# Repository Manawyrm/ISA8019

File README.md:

# ISA8019
ISA8019 is a modern, open-source hardware design for an ISA-bus network card.
It uses an RTL8019 chipset and is NE2000-compatible, which makes it easy to use with just about any operating system or software available. 

The design is optimized for automated assembly at [JLCPCB](https://jlcpcb.com/DDE). 

Only the RJ45 jack, jumper headers and the DIP-32 socket for the Boot ROM have to be soldered. 
Jumpers and Boot ROM are optional, the card can be used without any jumpers configured. 

Configuration can be done in 3 modes: 
- Jumper mode (JP jumper set)  
This mode allows for manual configuration of any parameters (I/O address, IRQ, BROM address & size, etc.) manually via jumpers. Refer to the back of the PCB for details. 
- EEPROM mode (also called "Jumperless", no jumpers set)  
In this mode, all parameters can be configured via the RSET8019.EXE dos utility and will be stored in the 9364 I²C EEPROM.
- PNP mode (no jumpers set)  
For modern computers and operating systems like Windows 9x or Linux, this mode is ideal. Resource management will be done by the BIOS or OS.

### Details
[Rev. A - Schematic](PCB/gerbers/RevA/ISA8019.pdf)  
[Rev. A - Interactive BOM](https://tbspace.de/content/downloads/isa8019_ibom.html)  
[Rev. A - Gerbers & Production files](PCB/gerbers/RevA/ISA8019/ISA8019.zip)  

### Drivers
[Official Realtek drivers, Windows 3.11, 9x, NT](https://github.com/Manawyrm/ISA8019/tree/master/Drivers/Official%20Realtek%20drivers)  
[MS-DOS packet drivers, for 16-bit machines](Drivers/Crynwr%20packet%20driver%20-%2016bit%20ISA)  
[MS-DOS packet drivers, modded for 8-bit XT machines](Drivers/Crynwr%20packet%20driver%20-%20modified%20for%208bit%20operation)  

### Programming utilities
[RSET8019.EXE](Programming%20utilities/Rset8019.exe) for DOS, can set EEPROM parameters, also includes diagnostic functions  
[pg8019](Programming%20utilities/pg8019) for DOS, can initialize EEPROM, set MAC address, vendor/product IDs  

### Errata
Rev.A - Soldermask over ISA slot

[https://tbspace.de](https://tbspace.de)

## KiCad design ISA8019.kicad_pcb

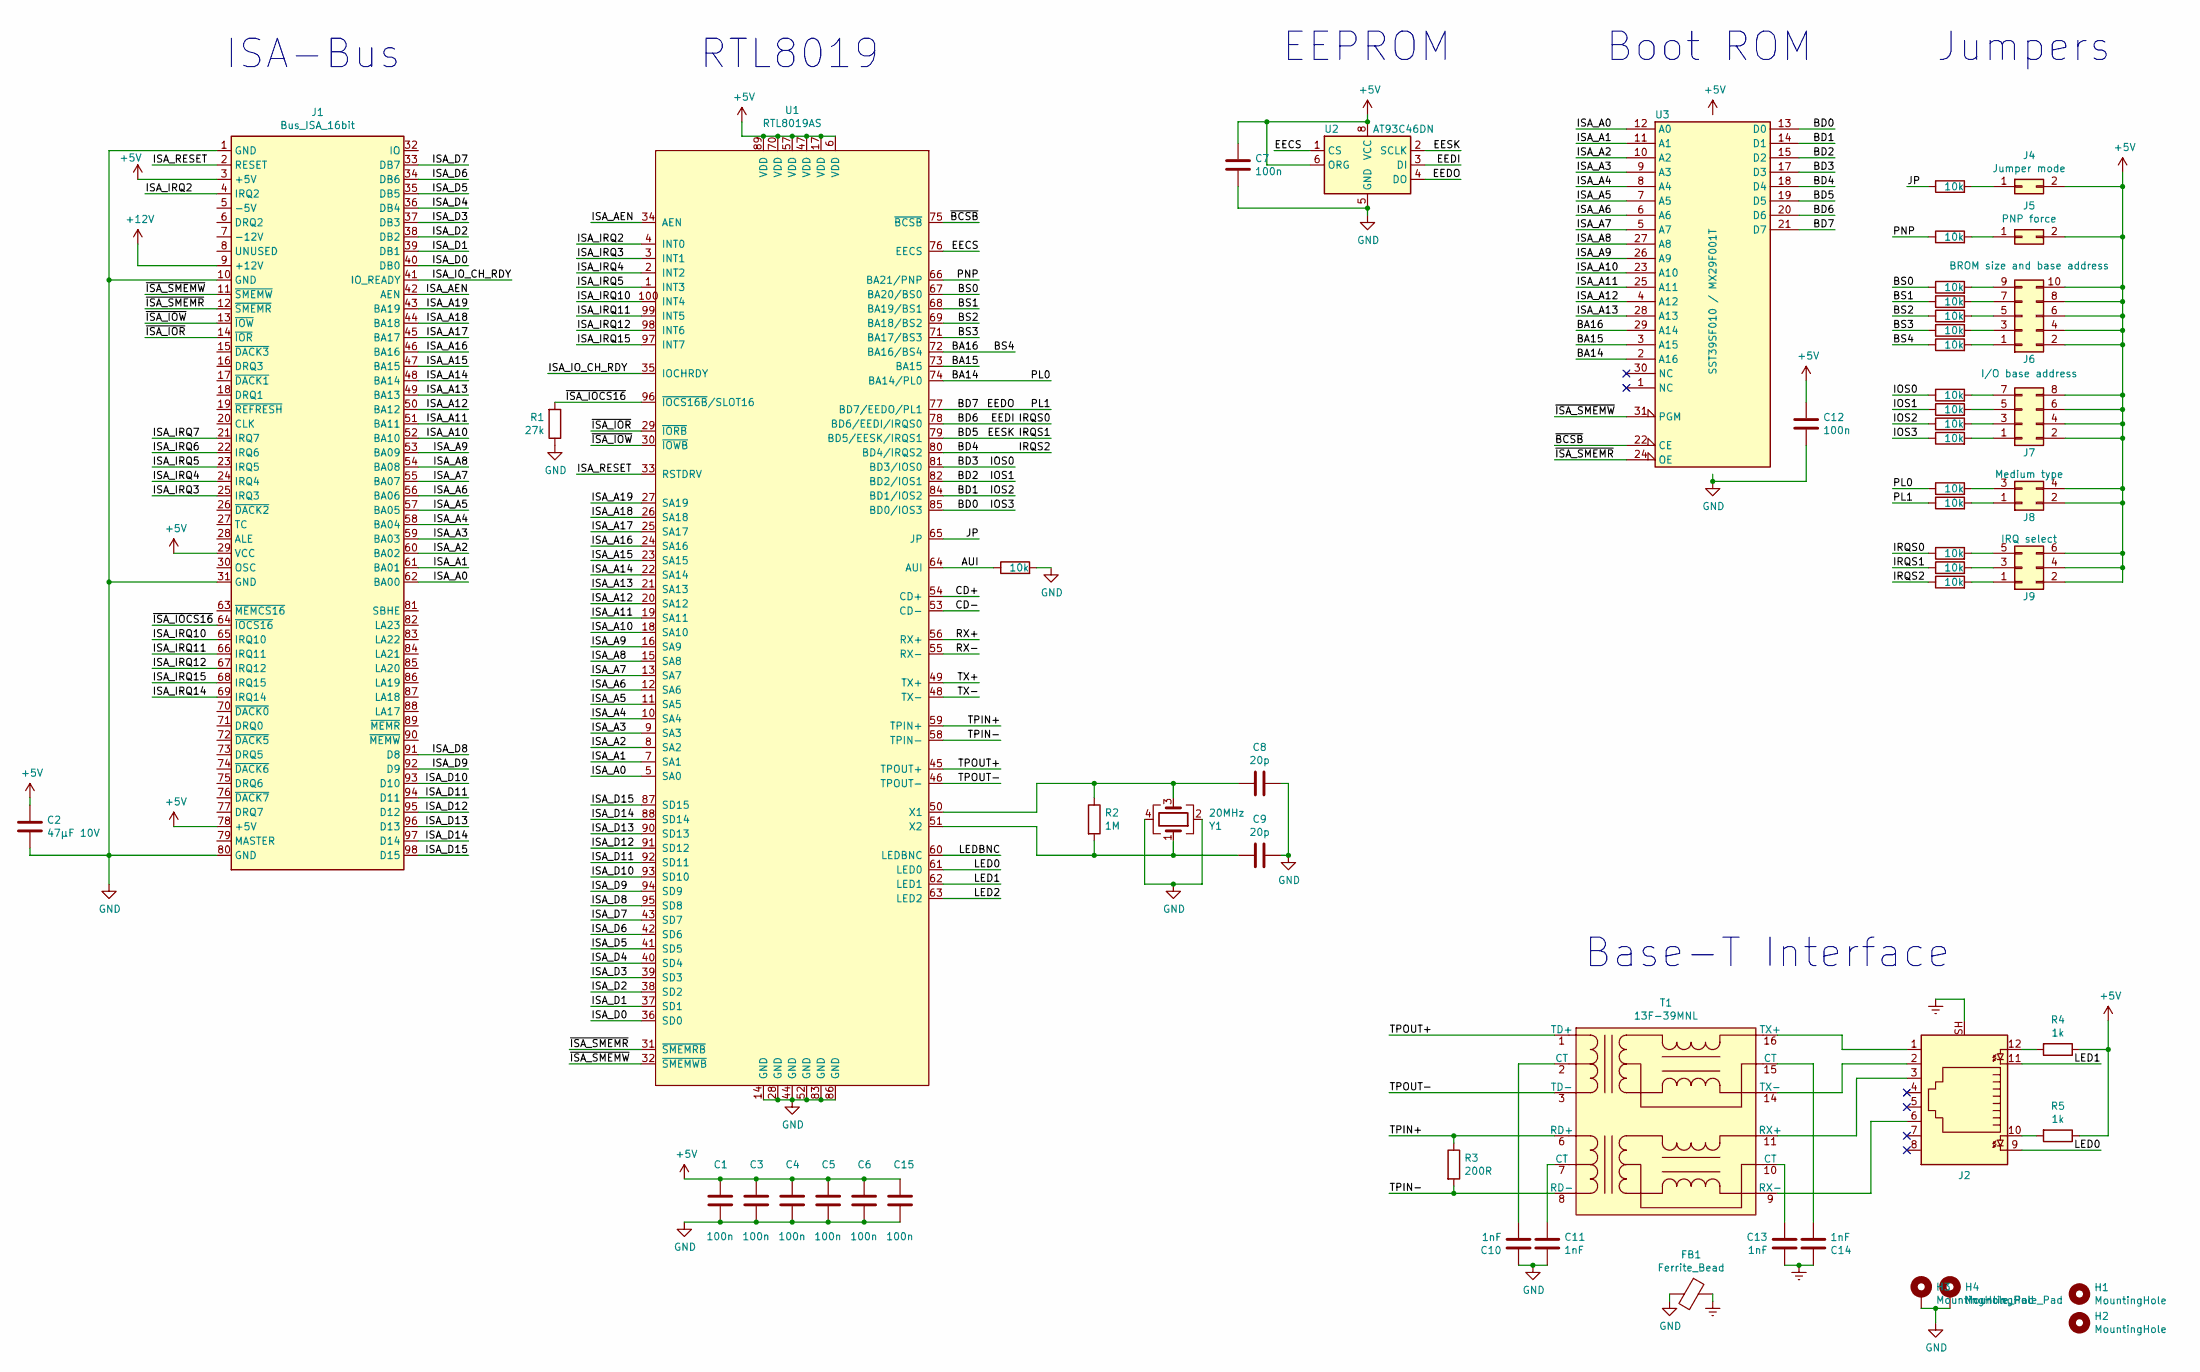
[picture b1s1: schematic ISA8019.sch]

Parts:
C1, C3, C4, C5, C6, C7, C12, C15: 100n; C_0402_1005Metric; LCSC C1525
C2: 47µF 10V; C_1206_3216Metric; LCSC C96123
C8, C9: 20p; C_0402_1005Metric; LCSC C1554
C10, C11, C13, C14: 1nF; C_1206_3216Metric; LCSC C9196
FB1: Ferrite_Bead; L_0805_2012Metric; LCSC C1017
H1, H2: MountingHole; ToolingHole_JLCSMT
H3, H4: MountingHole_Pad; MountingHole_3.2mm_M3_Pad_Via
J1: Bus_ISA_16bit; BUS_AT
J2: 8P8C_Shielded; 8P8C_yellow_green_Ckmtw_C133529
J4: Jumper mode; PinHeader_2x01_P2.54mm_Vertical
J5: PNP force; PinHeader_2x01_P2.54mm_Vertical
J6: BROM size and base address; PinHeader_2x05_P2.54mm_Vertical
J7: I/O base address; PinHeader_2x04_P2.54mm_Vertical
J8: Medium type; PinHeader_2x02_P2.54mm_Vertical
J9: IRQ select; PinHeader_2x03_P2.54mm_Vertical
R1: 27k; R_0402_1005Metric; LCSC C25771
R2: 1M; R_0402_1005Metric; LCSC C26083
R3: 200R; R_0402_1005Metric; LCSC C25087
R4, R5: 1k; R_0402_1005Metric; LCSC C11702
R6, R7, R8, R9, R10, R11, R12, R13, R14, R15, R16, R17, R18, R19, R20, R21, R22: 10k; R_0402_1005Metric; LCSC C25744
T1: 13F-39MNL; SOIC-16W-12_7.5x10.3mm_P1.27mm; LCSC C115949
U1: RTL8019AS; LQFP-14x20mm_P0.5mm; LCSC C10016
U2: AT93C46DN; SOIC-8_3.9x4.9mm_P1.27mm; LCSC C6499
U3: SST39SF010 / MX29F001T; DIP-32_W15.24mm_Socket_LongPads
Y1: 20MHz; Crystal_SMD_3225-4Pin_3.2x2.5mm; LCSC C110936

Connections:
+5V: C1.1, C2.1, C3.1, C4.1, C5.1, C6.1, C7.1, C12.1, C15.1, J1.3 (+5V), J1.29 (VCC), J1.78 (+5V), J4.2, J5.2, J6.2, J6.4, J6.6, J6.8, J6.10, J7.2, J7.4, J7.6, J7.8, J8.2, J8.4, J9.2, J9.4, J9.6, R4.1, R5.1, U1.6 (VDD), U1.17 (VDD), U1.47 (VDD), U1.57 (VDD), U1.70 (VDD), U1.89 (VDD), U2.6 (ORG), U2.8 (VCC), U3.32 (VCC)
+12V: J1.9 (+12V)
/AUI: R6.1, U1.64 (AUI)
/BA14: R18.1, U1.74 (BA14/PL0), U3.2 (A16)
/BA15: U1.73 (BA15), U3.3 (A15)
/BA16: R13.1, U1.72 (BA16/BS4), U3.29 (A14)
/BD0: R17.1, U1.85 (BD0/IOS3), U3.13 (D0)
/BD1: R16.1, U1.84 (BD1/IOS2), U3.14 (D1)
/BD2: R15.1, U1.82 (BD2/IOS1), U3.15 (D2)
/BD3: R14.1, U1.81 (BD3/IOS0), U3.17 (D3)
/BD4: R22.1, U1.80 (BD4/IRQS2), U3.18 (D4)
/BD5: R21.1, U1.79 (BD5/EESK/IRQS1), U2.2 (SCLK), U3.19 (D5)
/BD6: R20.1, U1.78 (BD6/EEDI/IRQS0), U2.3 (DI), U3.20 (D6)
/BD7: R19.1, U1.77 (BD7/EEDO/PL1), U2.4 (DO), U3.21 (D7)
/BS0: R9.1, U1.67 (BA20/BS0)
/BS1: R10.1, U1.68 (BA19/BS1)
/BS2: R11.1, U1.69 (BA18/BS2)
/BS3: R12.1, U1.71 (BA17/BS3)
/CD+: U1.54 (CD+)
/CD-: U1.53 (CD-)
/EECS: U1.76 (EECS), U2.1 (CS)
/ISA_A0: J1.62 (BA00), U1.5 (SA0), U3.12 (A0)
/ISA_A1: J1.61 (BA01), U1.7 (SA1), U3.11 (A1)
/ISA_A2: J1.60 (BA02), U1.8 (SA2), U3.10 (A2)
/ISA_A3: J1.59 (BA03), U1.9 (SA3), U3.9 (A3)
/ISA_A4: J1.58 (BA04), U1.10 (SA4), U3.8 (A4)
/ISA_A5: J1.57 (BA05), U1.11 (SA5), U3.7 (A5)
/ISA_A6: J1.56 (BA06), U1.12 (SA6), U3.6 (A6)
/ISA_A7: J1.55 (BA07), U1.13 (SA7), U3.5 (A7)
/ISA_A8: J1.54 (BA08), U1.15 (SA8), U3.27 (A8)
/ISA_A9: J1.53 (BA09), U1.16 (SA9), U3.26 (A9)
/ISA_A10: J1.52 (BA10), U1.18 (SA10), U3.23 (A10)
/ISA_A11: J1.51 (BA11), U1.19 (SA11), U3.25 (A11)
/ISA_A12: J1.50 (BA12), U1.20 (SA12), U3.4 (A12)
/ISA_A13: J1.49 (BA13), U1.21 (SA13), U3.28 (A13)
/ISA_A14: J1.48 (BA14), U1.22 (SA14)
/ISA_A15: J1.47 (BA15), U1.23 (SA15)
/ISA_A16: J1.46 (BA16), U1.24 (SA16)
/ISA_A17: J1.45 (BA17), U1.25 (SA17)
/ISA_A18: J1.44 (BA18), U1.26 (SA18)
/ISA_A19: J1.43 (BA19), U1.27 (SA19)
/ISA_AEN: J1.42 (AEN), U1.34 (AEN)
/ISA_D0: J1.40 (DB0), U1.36 (SD0)
/ISA_D1: J1.39 (DB1), U1.37 (SD1)
/ISA_D2: J1.38 (DB2), U1.38 (SD2)
/ISA_D3: J1.37 (DB3), U1.39 (SD3)
/ISA_D4: J1.36 (DB4), U1.40 (SD4)
/ISA_D5: J1.35 (DB5), U1.41 (SD5)
/ISA_D6: J1.34 (DB6), U1.42 (SD6)
/ISA_D7: J1.33 (DB7), U1.43 (SD7)
/ISA_D8: J1.91 (D8), U1.95 (SD8)
/ISA_D9: J1.92 (D9), U1.94 (SD9)
/ISA_D10: J1.93 (D10), U1.93 (SD10)
/ISA_D11: J1.94 (D11), U1.92 (SD11)
/ISA_D12: J1.95 (D12), U1.91 (SD12)
/ISA_D13: J1.96 (D13), U1.90 (SD13)
/ISA_D14: J1.97 (D14), U1.88 (SD14)
/ISA_D15: J1.98 (D15), U1.87 (SD15)
/ISA_IO_CH_RDY: J1.41 (IO_READY), U1.35 (IOCHRDY)
/ISA_IRQ2: J1.4 (IRQ2), U1.4 (INT0)
/ISA_IRQ3: J1.25 (IRQ3), U1.3 (INT1)
/ISA_IRQ4: J1.24 (IRQ4), U1.2 (INT2)
/ISA_IRQ5: J1.23 (IRQ5), U1.1 (INT3)
/ISA_IRQ6: J1.22 (IRQ6)
/ISA_IRQ7: J1.21 (IRQ7)
/ISA_IRQ10: J1.65 (IRQ10), U1.100 (INT4)
/ISA_IRQ11: J1.66 (IRQ11), U1.99 (INT5)
/ISA_IRQ12: J1.67 (IRQ12), U1.98 (INT6)
/ISA_IRQ14: J1.69 (IRQ14)
/ISA_IRQ15: J1.68 (IRQ15), U1.97 (INT7)
/ISA_RESET: J1.2 (RESET), U1.33 (RSTDRV)
/JP: R7.1, U1.65 (JP)
/LED0: J2.9, U1.61 (LED0)
/LED1: J2.11, U1.62 (LED1)
/LED2: U1.63 (LED2)
/LEDBNC: U1.60 (LEDBNC)
/PNP: R8.1, U1.66 (BA21/PNP)
/RX+: U1.56 (RX+)
/RX-: U1.55 (RX-)
/TPIN+: R3.1, T1.6 (RD+), U1.59 (TPIN+)
/TPIN-: R3.2, T1.8 (RD-), U1.58 (TPIN-)
/TPOUT+: T1.1 (TD+), U1.45 (TPOUT+)
/TPOUT-: T1.3 (TD-), U1.46 (TPOUT-)
/TX+: U1.49 (TX+)
/TX-: U1.48 (TX-)
/~BCSB: U1.75 (~BCSB), U3.22 (CE)
/~ISA_IOCS16: J1.64 (~IOCS16), R1.2, U1.96 (~IOCS16B~/SLOT16)
/~ISA_IOR: J1.14 (~IOR), U1.29 (~IORB)
/~ISA_IOW: J1.13 (~IOW), U1.30 (~IOWB)
/~ISA_SMEMR: J1.12 (~SMEMR), U1.31 (~SMEMRB), U3.24 (OE)
/~ISA_SMEMW: J1.11 (~SMEMW), U1.32 (~SMEMWB), U3.31 (PGM)
Earth: C13.2, C14.1, FB1.1, J2.SH
GND: C1.2, C2.2, C3.2, C4.2, C5.2, C6.2, C7.2, C8.1, C9.1, C10.1, C11.2, C12.2, C15.2, FB1.2, H3.1, H4.1, J1.1 (GND), J1.10 (GND), J1.31 (GND), J1.80 (GND), R1.1, R6.2, U1.14 (GND), U1.28 (GND), U1.44 (GND), U1.52 (GND), U1.83 (GND), U1.86 (GND), U2.5 (GND), U3.16 (GND), Y1.2, Y1.4
unnamed: C8.2, R2.1, U1.50 (X1), Y1.3
unnamed: C9.2, R2.2, U1.51 (X2), Y1.1
unnamed: C10.2, T1.2 (CT)
unnamed: C11.1, T1.7 (CT)
unnamed: C13.1, T1.10 (CT)
unnamed: C14.2, T1.15 (CT)
unnamed: J2.1, T1.16 (TX+)
unnamed: J2.2, T1.14 (TX-)
unnamed: J2.3, T1.11 (RX+)
unnamed: J2.6, T1.9 (RX-)
unnamed: J2.10, R5.2
unnamed: J2.12, R4.2
unnamed: J4.1, R7.2
unnamed: J5.1, R8.2
unnamed: J6.1, R13.2
unnamed: J6.3, R12.2
unnamed: J6.5, R11.2
unnamed: J6.7, R10.2
unnamed: J6.9, R9.2
unnamed: J7.1, R17.2
unnamed: J7.3, R16.2
unnamed: J7.5, R15.2
unnamed: J7.7, R14.2
unnamed: J8.1, R19.2
unnamed: J8.3, R18.2
unnamed: J9.1, R22.2
unnamed: J9.3, R21.2
unnamed: J9.5, R20.2

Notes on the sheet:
Base-T Interface
ISA-Bus
RTL8019
Boot ROM
Jumpers
EEPROM

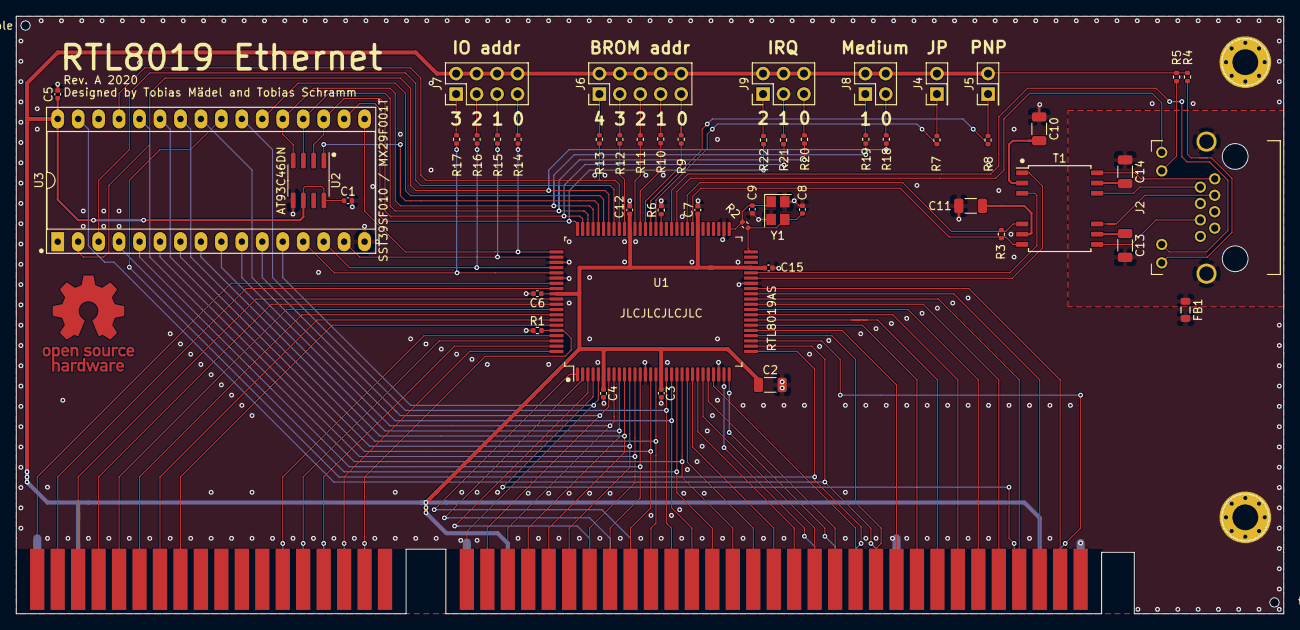
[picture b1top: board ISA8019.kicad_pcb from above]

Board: 2 copper layers, 157.4 x 74.2 mm, 56 parts (0 on the bottom side), 109 nets.

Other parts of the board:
H5: OSHW Logo; OSHW-Logo_11.4x12mm_Copper

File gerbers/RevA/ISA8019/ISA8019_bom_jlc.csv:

"Comment","Designator","Footprint","LCSC Part #"
"100n","C1,C3,C4,C5,C6,C15,C12,C7","C_0402_1005Metric","C1525"
"47µF 10V","C2","C_1206_3216Metric","C96123"
"20p","C8,C9","C_0402_1005Metric","C1554"
"1nF","C11,C10,C13,C14","C_1206_3216Metric","C9196"
"Ferrite_Bead","FB1","L_0805_2012Metric","C1017"
"27k","R1","R_0402_1005Metric","C25771"
"1M","R2","R_0402_1005Metric","C26083"
"200R","R3","R_0402_1005Metric","C25087"
"1k","R4,R5","R_0402_1005Metric","C11702"
"10k","R7,R8,R9,R10,R11,R12,R13,R14,R15,R16,R17,R18,R19,R20,R21,R22,R6","R_0402_1005Metric","C25744"
"13F-39MNL","T1","SOIC-16W-12_7.5x10.3mm_P1.27mm","C115949"
"RTL8019AS","U1","LQFP-14x20mm_P0.5mm","C10016"
"AT93C46DN","U2","SOIC-8_3.9x4.9mm_P1.27mm","C6499"
"20MHz","Y1","Crystal_SMD_3225-4Pin_3.2x2.5mm","C110936"

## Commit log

2020-11-10 Map pins, add pin type, symbol done
2020-11-12 Add schematic, copy parts of RC2014-Ethernet
2020-11-12 Add EEPROM and boot flash
2020-11-12 Add jumpers, AUI interface
2020-11-13 Add mechanicals
2020-11-14 Some routing
2020-11-14 some routing later
2020-11-14 Redo most of the bus layout
2020-11-14 Fix BA14/BA15 spacing below ROM
2020-11-14 Route all nets
2020-11-15 Add silkscreen and jumper settings
2020-11-15 Add JLC markings, manufacturing details and new gerbers
2020-11-15 More GND via stitching and minor aesthetic fixes
2020-11-15 Small trace cleanup and new gerbers
2020-12-03 Create LICENSE
2020-12-03 Add schematic .pdf, drivers, programming utilities
